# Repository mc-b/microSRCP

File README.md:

microSRCP
=========

microSRCP Projekt, Steuerung einer Modelleisenbahn auf Basis der Arduino Plattform

Dieses Projekt löst das microSRCP Projekt auf berlios.de ab.

Kurzinstallation:
- Arduino Entwicklungsumgebung - http://arduino.cc/en/Main/Software, ab Version 1.0.5 installieren
- RocRail - http://wiki.rocrail.net/doku.php, zur Ansteuerung der Modelleisenbahn und der Arduino's, installieren
- Arduino Entwicklungsumgebung starten und Verzeichnis aus Menu -> Datei -> Einstellungen -> Sketchbook Speicherort notieren
- Entwicklungsumgebung beenden
- gewünschte ZIP/tar-Datei von https://github.com/mc-b/microSRCP/tags auswählen und downloaden
- ZIP/tar Datei entpacken und die Dateien aus Verzeichnis .../microSRCP/arduino in den vorher notierten Sketchbook Speicherort kopieren.
- Arduino Entwicklungsumgebung starten - unter -> Datei -> Sketchbook -> microSRCPServer wählen
- PC und Arduino mittels USB Kabel verbinden, das Betriebssystem richtet eine neue Serielle Schnittstelle ein (bei Problemen siehe www.arduino.cc)
- Unter Tools -> entsprechendes Board und Serielle Schnittstelle einstellen
- Compilieren und Uploaden des Sketches...
- RocRail starten und unter -> RocRail Eigenschaften neue srcp Zentrale mit Sub Bibliothek RS232 und gleicher Serieller Schnittstelle wie bei der Arduino Entwicklungsumgebung einrichten

Welche Arduino Boards und Shields benötigt werden steht in den entsprechenden Sketches. 

Für eine Detailierte Beschreibung, siehe https://github.com/mc-b/microSRCP/wiki.

Copyright
---------
Die Software untersteht der GNU GPL, siehe entsprechende Copyrights in 
den Sourcen. Da bedeutet u.a., sie kann frei verwendet werden, Aenderungen
und Erweiterungen muessen aber wieder frei zugaenglich sein.
Kommerzielle Produkte, ohne Offenlegung des Codes, sind damit ausgeschlossen!

Haftung
-------
Bei den Bauanleitungen bzw. irgendwelcher Software gibt es keine Haftung fuer 
irgendwelche Schaeden oder Funktionsgarantie, bitte immer nur als Anregung auffassen.
Ich hafte nicht fuer Schaeden, die der Anwender oder Dritte durch die Verwendung der 
Software oder Hardware verursachen oder erleiden. In keinem Fall hafte ich fuer 
entgangenen Umsatz oder Gewinn oder sonstige Vermoegensschaeden die bei der Verwendung 
oder durch die Verwendung dieser Programme oder Anleitungen entstehen koennen.
Und wer mit Strom umgeht, soll sich bitte bei hoeheren Spannung und Stroemen der 
Gefahren bewusst sein. Modellbahn gehoert VDE-technisch zur Kategorie Spielzeug, 
dementsprechend streng sind die Vorschriften. Siehe hierzu auch die 
Sicherheitshinweise des Fremo. 

Die Schaltungen und die Software werden als Anregung und Hilfe unter Modellbahnern
veroeffentlicht. Sie sind auf Grund von Beispielen aus dem Netz bzw. eigenen Ideen 
entstanden. Natuerlich sind sinnvolle Anregungen, Fehlermeldungen und 
Verbesserungen zu den Schaltung immer willkommen. Allerdings moechte ich aus 
gegebenen Anlass darauf hinweisen, dass ich leider keine Zeit fuer langwierige 
Diskussionen des Typs "Ich habe die Schaltung nachgebaut, warum funktioniert 
sie bei mir nicht" habe. Auch die Frage "Ich habe noch diesen oder jenen Chip 
in der Schublade, kann ich den auch verwenden", moege sich bitte jeder selbst 
beantworten. Kontaktaufnahme bitte per mail und nicht per Telefon. 
Bitte bei Problemen moeglichst exakt schildern, was wie schief geht, 
am besten mit logfiles bzw. exakter Fehlermeldung.

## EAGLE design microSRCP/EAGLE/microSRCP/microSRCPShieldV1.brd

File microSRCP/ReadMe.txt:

Sourcen fuer Arduino IDE und Beispieldateien RocRail.

Arduino IDE
-----------
Dateien aus dem microSRCP/arduino Verzeichnis in Arduino Sketchbook-
Verzeichnis kopieren (siehe File -> Preferences in der 
Arduino IDE).

Mittels File -> Sketchbook koennen dann die einzelne
Board Sketches geoeffnet, compiliert und ins Board
geladen werden.

RocRail
-------
Die SRCP Zentrale kann einfach mittels dem User-Interface von 
RocRail erstellt werden.

Dazu ist eine srcp Zentrale einzutragen und je nach Sketch
die Sub Bibliothek TCPIP oder RS232 einzutragen.

In den Verzeichnissen RocRail befinden sich Beispiele der
rocrail.ini (Konfiguration Zentrale) und dazupassende
plan.xml Dateien.

Copyright
---------
Die Software untersteht der GNU GPL, siehe entsprechende Copyrights in 
den Sourcen. Da bedeutet u.a., sie kann frei verwendet werden, Aenderungen
und Erweiterungen muessen aber wieder frei zugaenglich sein.
Kommerzielle Produkte, ohne Offenlegung des Codes, sind damit ausgeschlossen!

Haftung
-------
Bei den Bauanleitungen bzw. irgendwelcher Software gibt es keine Haftung fuer 
irgendwelche Schaeden oder Funktionsgarantie, bitte immer nur als Anregung auffassen.
Ich hafte nicht fuer Schaeden, die der Anwender oder Dritte durch die Verwendung der 
Software oder Hardware verursachen oder erleiden. In keinem Fall hafte ich fuer 
entgangenen Umsatz oder Gewinn oder sonstige Vermoegensschaeden die bei der Verwendung 
oder durch die Verwendung dieser Programme oder Anleitungen entstehen koennen.
Und wer mit Strom umgeht, soll sich bitte bei hoeheren Spannung und Stroemen der 
Gefahren bewusst sein. Modellbahn gehoert VDE-technisch zur Kategorie Spielzeug, 
dementsprechend streng sind die Vorschriften. Siehe hierzu auch die 
Sicherheitshinweise des Fremo. 

Die Schaltungen und die Software werden als Anregung und Hilfe unter Modellbahnern
veroeffentlicht. Sie sind auf Grund von Beispielen aus dem Netz bzw. eigenen Ideen 
entstanden. Natuerlich sind sinnvolle Anregungen, Fehlermeldungen und 
Verbesserungen zu den Schaltung immer willkommen. Allerdings moechte ich aus 
gegebenen Anlass darauf hinweisen, dass ich leider keine Zeit fuer langwierige 
Diskussionen des Typs "Ich habe die Schaltung nachgebaut, warum funktioniert 
sie bei mir nicht" habe. Auch die Frage "Ich habe noch diesen oder jenen Chip 
in der Schublade, kann ich den auch verwenden", moege sich bitte jeder selbst 
beantworten. Kontaktaufnahme bitte per mail und nicht per Telefon. 
Bitte bei Problemen moeglichst exakt schildern, was wie schief geht, 
am besten mit logfiles bzw. exakter Fehlermeldung. 

8. Mai 2013 / Marcel Bernet

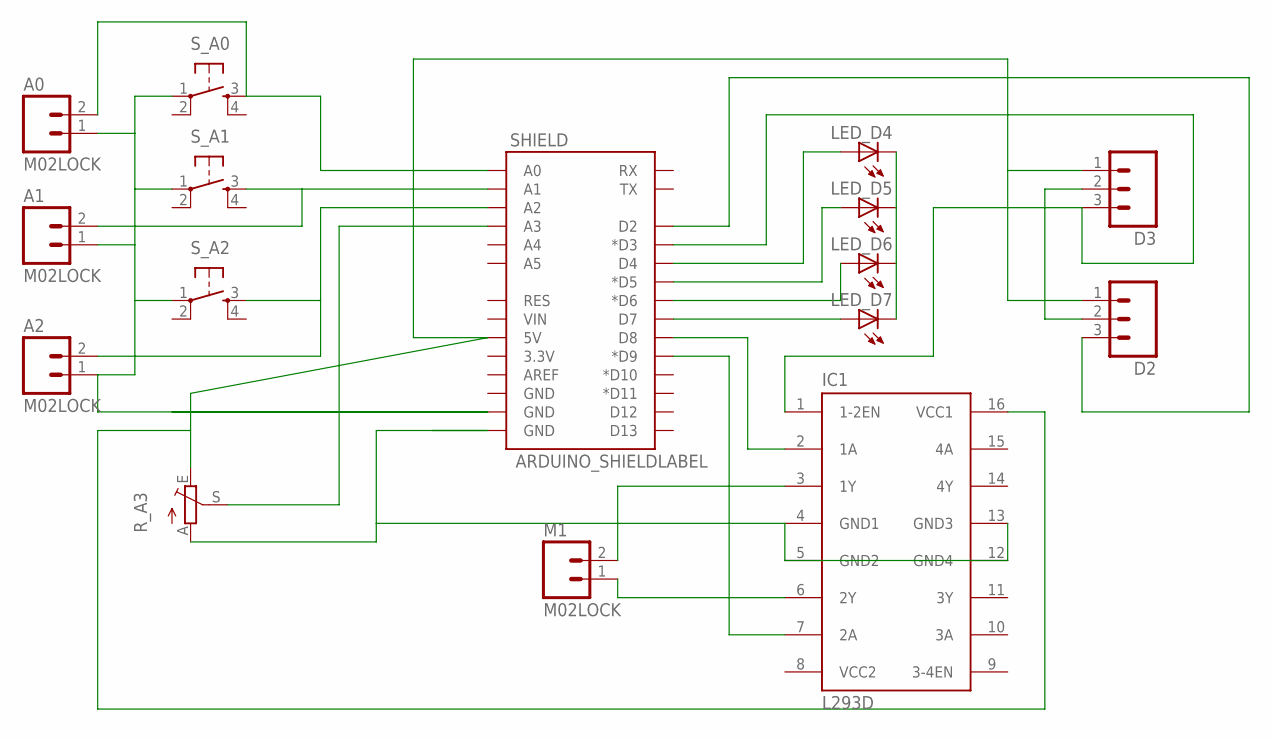
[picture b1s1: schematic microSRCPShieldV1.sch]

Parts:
A0, A1, A2: M02LOCK; 1X02_LOCK
D2, D3: M03LOCK; 1X03_LOCK
IC1: L293D; DIL16
LED_D4, LED_D5, LED_D6, LED_D7: LED3MM
M1: M02LOCK; 1X02_LOCK
R_A3: TRIM_EU-PT10S; PT-10S
SHIELD: ARDUINO_SHIELDLABEL; DUEMILANOVE_SHIELD
S_A0, S_A1, S_A2: TAC_SWITCHPTH; TACTILE-PTH

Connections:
unnamed: A1.2, SHIELD.A1, S_A1.3
unnamed: LED_D6.A, SHIELD.D6 (*D6)
unnamed: LED_D5.A, SHIELD.D5 (*D5)
unnamed: LED_D4.A, SHIELD.D4
unnamed: LED_D4.K (C), LED_D5.K (C), LED_D6.K (C), LED_D7.K (C)
unnamed: A2.2, SHIELD.A2, S_A2.3
unnamed: LED_D7.A, SHIELD.D7
unnamed: A0.2, SHIELD.A0, S_A0.3
unnamed: IC1.2 (1A), SHIELD.D8
unnamed: IC1.7 (2A), SHIELD.D9 (*D9)
unnamed: D2.1, D3.1, IC1.16 (VCC1), R_A3.E, SHIELD.5V
unnamed: IC1.3 (1Y), M1.2
unnamed: IC1.6 (2Y), M1.1
unnamed: R_A3.S, SHIELD.A3
unnamed: A0.1, A1.1, A2.1, SHIELD.GND@1 (GND), S_A0.1, S_A1.1, S_A2.1
unnamed: IC1.4 (GND1), IC1.5 (GND2), IC1.12 (GND4), IC1.13 (GND3), R_A3.A, SHIELD.GND@0 (GND)
unnamed: D2.3, SHIELD.D2
unnamed: D3.3, IC1.1 (1-2EN), SHIELD.D3 (*D3)
unnamed: D2.2, D3.2
VCC2: IC1.8 (VCC2)

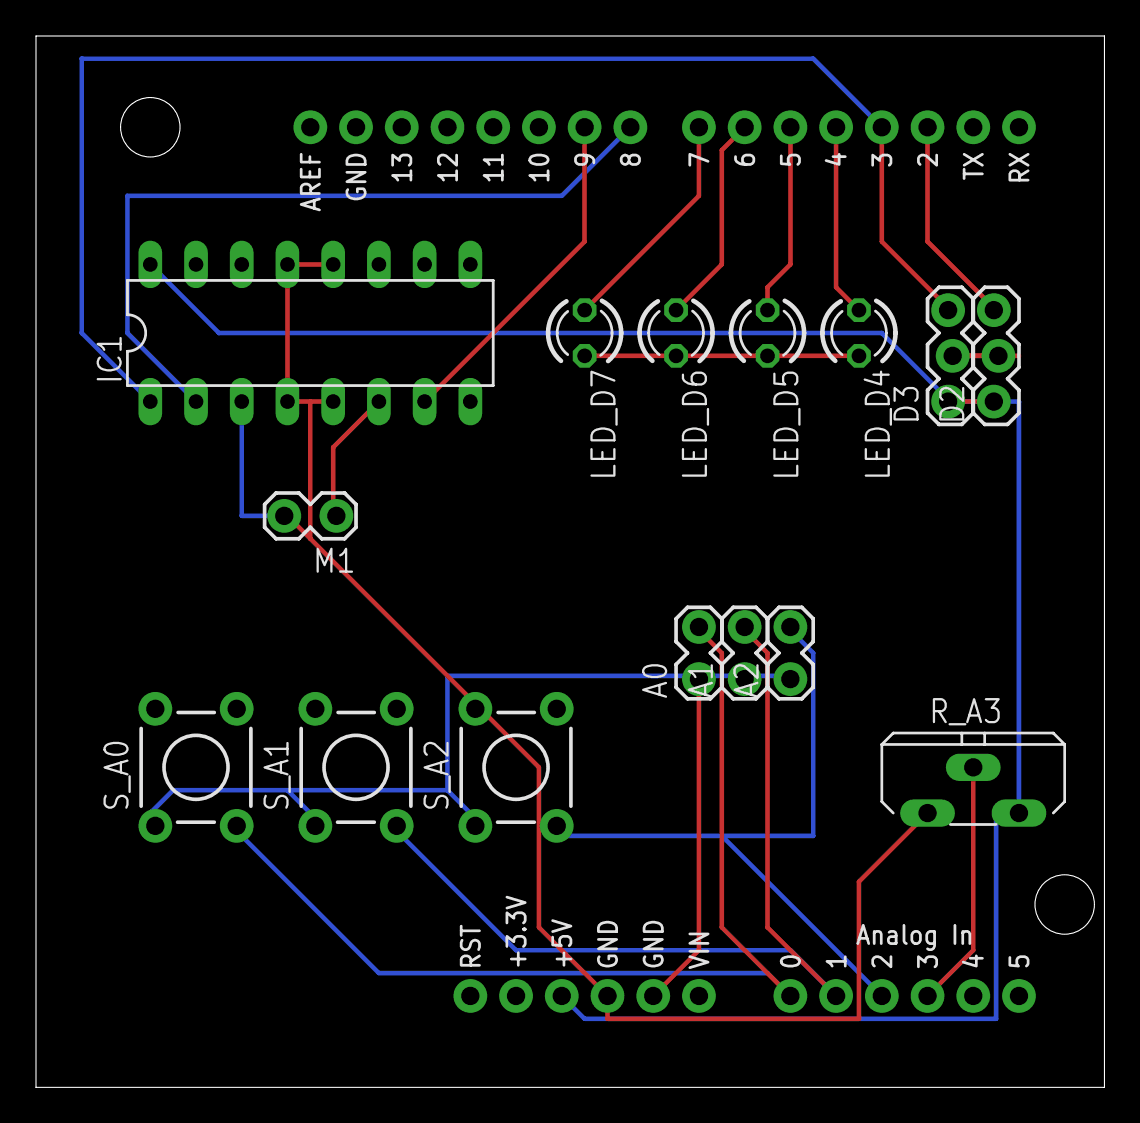
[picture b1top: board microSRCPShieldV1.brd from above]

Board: 2 copper layers, 59.4 x 58.4 mm, 16 parts (0 on the bottom side), 19 nets.

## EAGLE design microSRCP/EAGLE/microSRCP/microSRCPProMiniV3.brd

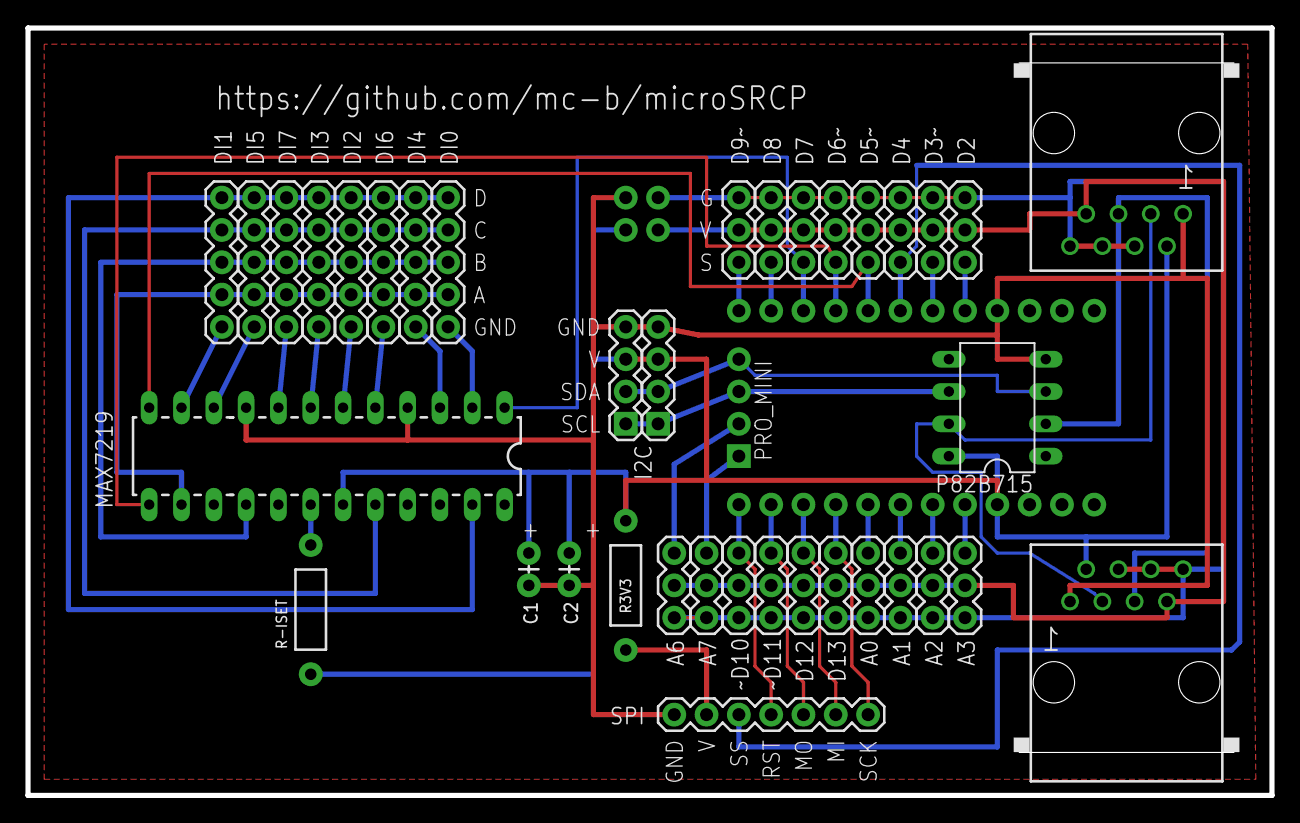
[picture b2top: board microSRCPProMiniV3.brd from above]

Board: 2 copper layers, 97.8 x 60.3 mm, 41 parts (0 on the bottom side), 40 nets.

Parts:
A0, A1, A2, A3, A6, A7: 1X03
C1, C2: AXIAL-0.1
D2, D3~, D4, D5~, D6~, D7, D8, D9~, D12, D13: 1X03
DI0, DI1, DI2, DI3, DI4, DI5, DI6, DI7: 1X05
E$1: 1X04_NO_SILK
E$2: 1X04
E$3: R3V3; AXIAL-0.4
E$4, E$5: RJ45-NO-SHIELD
GND: 1X02_NO_SILK
I2C: 1X04
MAX7219: DIL24
P82B715: DIL-08
PRO_MINI: ARDUINO_MINI
R-ISET: AXIAL-0.4
SPI: 1X07
V5: 1X02_NO_SILK
~D10, ~D11: 1X03

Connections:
2-5V: A0.2, A1.2, A2.2, A3.2, A6.2, A7.2, D2.2, D3~.2, D4.2, D5~.2, D6~.2, D7.2, D8.2, D9~.2, D12.2, D13.2, E$4.7, E$5.7, GND.1, ~D10.2, ~D11.2
2-GND: A0.1, A1.1, A2.1, A3.1, A6.1, A7.1, D2.3, D3~.3, D4.3, D5~.3, D6~.3, D7.3, D8.3, D9~.3, D12.1, D13.1, E$4.4, E$4.6, E$4.8, E$5.4, E$5.6, E$5.8, GND.2, ~D10.1, ~D11.1
5V: C1.P$2, C2.P$2, E$2.3, E$3.P$2, E$4.2, E$5.2, I2C.3, MAX7219.19, P82B715.8, PRO_MINI.21, R-ISET.P$1, V5.1
GND: C1.P$1, C2.P$1, E$2.4, E$4.1, E$5.1, I2C.4, MAX7219.4, MAX7219.9, P82B715.4, PRO_MINI.4, SPI.1, V5.2
LSDA: E$4.5, E$5.5, P82B715.2
LSDL: E$4.3, E$5.3, P82B715.7
S$1: E$3.P$1, SPI.2
S$2: D2.1, PRO_MINI.5
S$3: D3~.1, PRO_MINI.6
S$4: D4.1, PRO_MINI.7, SPI.3
S$5: D5~.1, MAX7219.12, PRO_MINI.8
S$6: D6~.1, MAX7219.13, PRO_MINI.9
S$7: D7.1, MAX7219.1, PRO_MINI.10
S$8: D8.1, PRO_MINI.11
S$9: D9~.1, PRO_MINI.12
S$10: PRO_MINI.13, SPI.4, ~D10.3
S$11: PRO_MINI.14, SPI.5, ~D11.3
S$12: D12.3, PRO_MINI.15, SPI.6
S$13: D13.3, PRO_MINI.16, SPI.7
S$14: A0.3, PRO_MINI.17
S$15: A1.3, PRO_MINI.18
S$16: A2.3, PRO_MINI.19
S$17: A3.3, PRO_MINI.20
S$18: DI0.1, MAX7219.2
S$19: DI4.1, MAX7219.3
S$20: DI6.1, MAX7219.5
S$21: DI2.1, MAX7219.6
S$22: DI3.1, MAX7219.7
S$23: DI7.1, MAX7219.8
S$24: DI5.1, MAX7219.10
S$25: DI1.1, MAX7219.11
S$26: DI0.2, DI1.2, DI2.2, DI3.2, DI4.2, DI5.2, DI6.2, DI7.2, MAX7219.14
S$27: MAX7219.18, R-ISET.P$2
S$28: DI0.4, DI1.4, DI2.4, DI3.4, DI4.4, DI5.4, DI6.4, DI7.4, MAX7219.20
S$29: DI0.5, DI1.5, DI2.5, DI3.5, DI4.5, DI5.5, DI6.5, DI7.5, MAX7219.23
S$32: DI0.3, DI1.3, DI2.3, DI3.3, DI4.3, DI5.3, DI6.3, DI7.3, MAX7219.16
S$A6: A6.3, E$1.2
S$A7: A7.3, E$1.1
SDA: E$1.4, E$2.2, I2C.2, P82B715.3
SDL: E$1.3, E$2.1, I2C.1, P82B715.6

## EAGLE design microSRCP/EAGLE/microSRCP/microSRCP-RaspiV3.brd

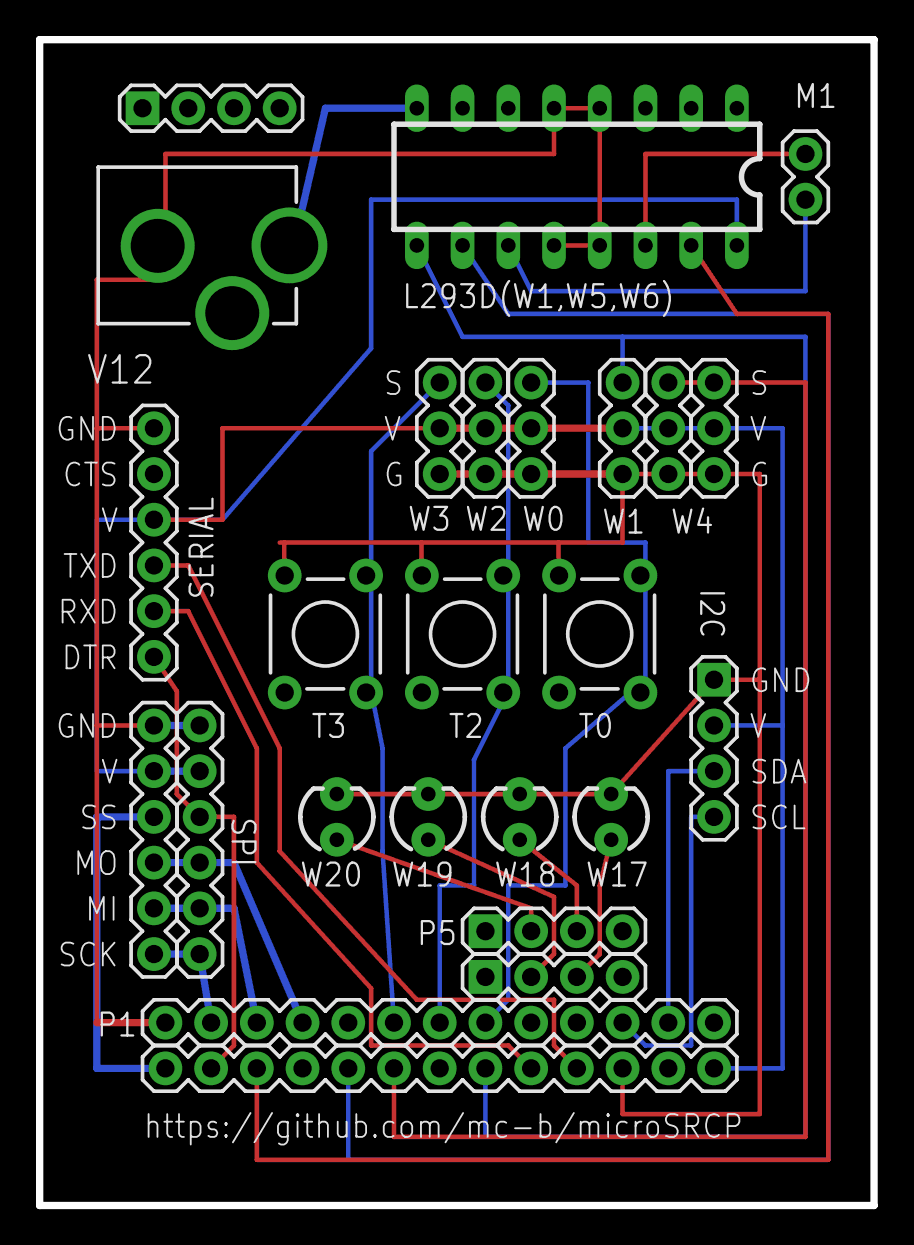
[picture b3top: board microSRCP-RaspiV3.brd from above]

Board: 2 copper layers, 46.4 x 64.8 mm, 25 parts (0 on the bottom side), 24 nets.

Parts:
E$1: 1X13
E$2, E$3: 1X04
E$5: 1X06
I2C: 1X04
L293D(W1,W5,W6): DIL16
M1: 1X02
P1: 1X13
P5: 1X04
SERIAL: 1X06
SPI: 1X06
T0, T2, T3: TACTILE-PTH
V12: POWER_JACK_PTH_LOCK
W0, W1, W1N, W2, W3, W4: 1X03
W17, W18, W19, W20: LED3MM

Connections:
5V: E$1.13, E$5.5, I2C.2, L293D(W1,W5,W6).16, SERIAL.4, SPI.2, W0.2, W1.2, W1N.2, W2.2, W3.2, W4.2
GND: E$1.11, E$5.6, I2C.1, L293D(W1,W5,W6).4, L293D(W1,W5,W6).5, L293D(W1,W5,W6).12, L293D(W1,W5,W6).13, P1.1, SERIAL.6, SPI.1, W0.1, W1.1, W1N.1, W2.1, W3.1, W4.1, W17.K, W18.K, W19.K, W20.K
S0: P1.8, W0.3
S1: E$1.8, L293D(W1,W5,W6).9, W4.3
S2: P1.7, W2.3
S3: P1.6, W3.3
S4: E$1.6, W1.3, W1N.3
S5: E$1.5, L293D(W1,W5,W6).10
S6: E$1.3, L293D(W1,W5,W6).15
S$2: E$5.1, P1.2, SPI.6
S$3: E$5.2, P1.3, SPI.5
S$4: E$5.3, P1.4, SPI.4
S$5: E$1.1, SPI.3
S$6: E$1.2, E$5.4, SERIAL.1
S$8: E$3.3, W17.A
S$10: P5.3, W18.A
S$11: E$3.2, W19.A
S$12: P5.2, W20.A
S$13: E$1.9, SERIAL.2
S$14: E$1.10, SERIAL.3
SM1L: L293D(W1,W5,W6).14, M1.1
SM1R: L293D(W1,W5,W6).11, M1.2
SSCL: I2C.4, P1.11
SSDA: I2C.3, P1.12

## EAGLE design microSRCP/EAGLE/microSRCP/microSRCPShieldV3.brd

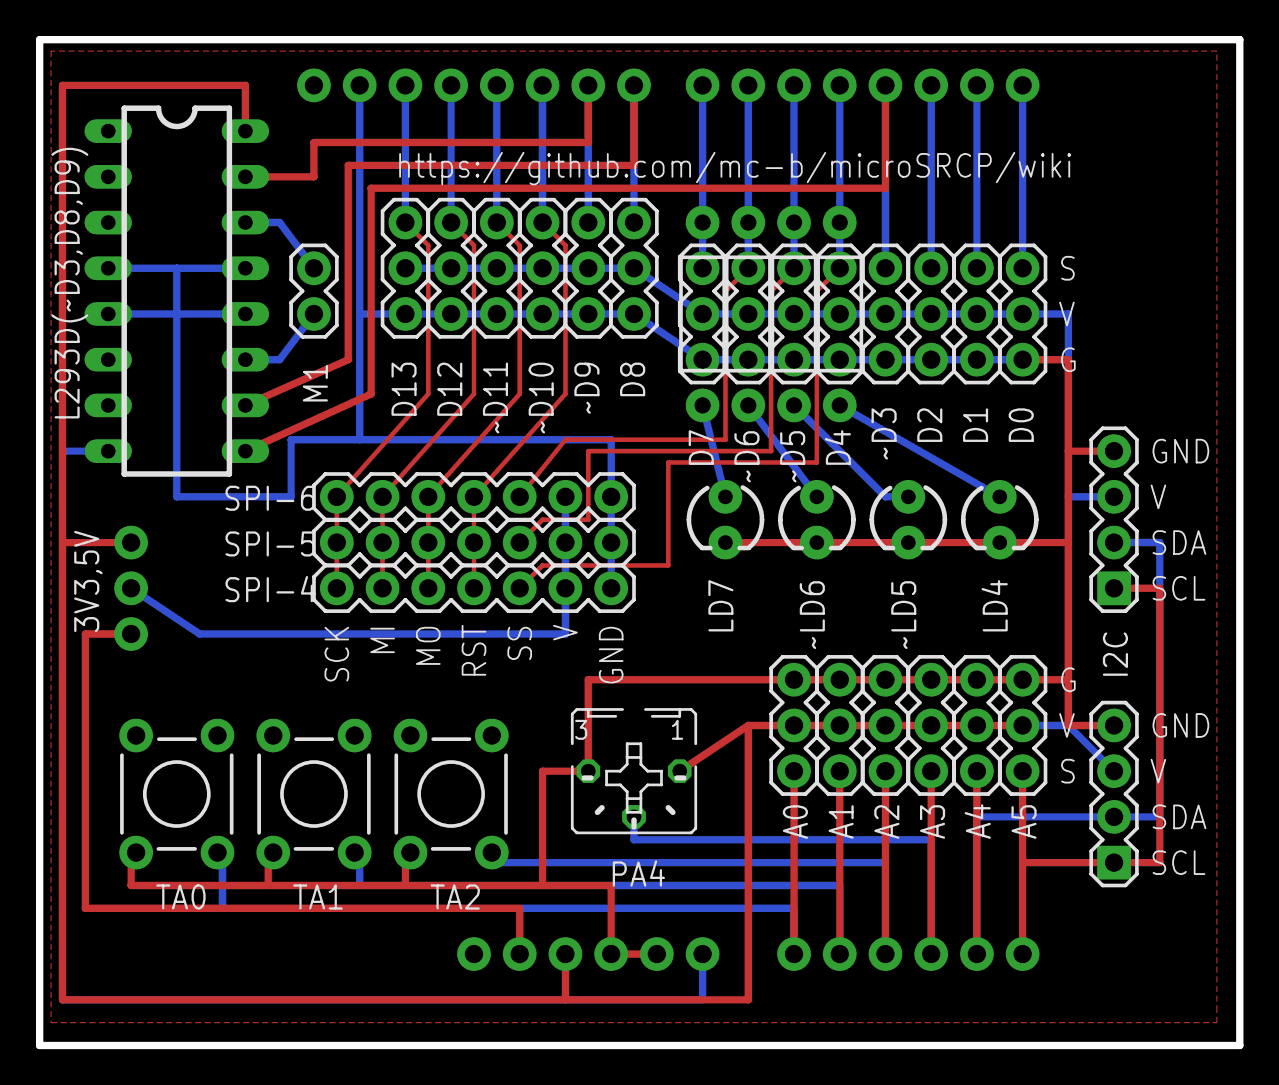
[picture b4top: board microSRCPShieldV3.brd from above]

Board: 2 copper layers, 66.7 x 55.9 mm, 41 parts (0 on the bottom side), 31 nets.

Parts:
3V3,5V: 1X03_NO_SILK
A0, A1, A2, A3, A4, A5: 1X03
D0, D1, D2, D4, D7, D8, D12, D13: 1X03
E$1: DUEMILANOVE_SHIELD_NOHOLES_NOLABELS
I2C, I2C-2: 1X04
L293D(~D3,D8,D9): DIL16
LD4, LD7: LED3MM
M1: 1X02
PA4: B25P
R1, R2, R3, R7: AXIAL-0.4
SPI-4, SPI-5, SPI-6: 1X07
TA0, TA1, TA2: TACTILE-PTH
~D3, ~D5, ~D6, ~D9, ~D10, ~D11: 1X03
~LD5, ~LD6: LED3MM

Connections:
GND: A0.3, A1.3, A2.3, A3.3, A4.3, A5.3, D0.3, D1.3, D2.3, D4.3, D7.3, D8.3, D12.3, D13.3, E$1.GND@0, E$1.GND@1, E$1.GND@2, I2C.4, I2C-2.4, L293D(~D3,D8,D9).4, L293D(~D3,D8,D9).5, L293D(~D3,D8,D9).12, L293D(~D3,D8,D9).13, LD4.K, LD7.K, PA4.E, SPI-4.7, SPI-5.7, SPI-6.7, ~D3.3, ~D5.3, ~D6.3, ~D9.3, ~D10.3, ~D11.3, ~LD5.K, ~LD6.K
S0: D0.1, E$1.RX
S1: D1.1, E$1.TX
S2: D2.1, E$1.D2
S3: E$1.D3, L293D(~D3,D8,D9).9, ~D3.1
S3V3: 3V3,5V.1, E$1.3.3V
S5: E$1.D5, R2.P$2, SPI-5.5, ~D5.1
S6: E$1.D6, R1.P$2, SPI-6.5, ~D6.1
S7: D7.1, E$1.D7, R7.P$2
S8: D8.1, E$1.D8, L293D(~D3,D8,D9).10
S10: E$1.D10, SPI-4.4, SPI-5.4, SPI-6.4, ~D10.1
S11: E$1.D11, SPI-4.3, SPI-5.3, SPI-6.3, ~D11.1
S12: D12.1, E$1.D12, SPI-4.2, SPI-5.2, SPI-6.2
S13: D13.1, E$1.D13, SPI-4.1, SPI-5.1, SPI-6.1
S$1: R2.P$1, ~LD5.A
S$2: 3V3,5V.2, SPI-4.6, SPI-5.6, SPI-6.6
S$3: E$1.D9, L293D(~D3,D8,D9).15, ~D9.1
S$4: D4.1, E$1.D4, R3.P$2, SPI-4.5
S$9: LD4.A, R3.P$1
S$11: R1.P$1, ~LD6.A
S$12: LD7.A, R7.P$1
SA0: A0.1, E$1.A0
SA1: A1.1, E$1.A1
SA2: A2.1, E$1.A2
SA3: A3.1, E$1.A3, PA4.S
SA4: A4.1, E$1.A4, I2C.2, I2C-2.2
SA5: A5.1, E$1.A5, I2C.1, I2C-2.1
SM1-L: L293D(~D3,D8,D9).14, M1.2
SM1R: L293D(~D3,D8,D9).11, M1.1
SVIN: E$1.VIN, L293D(~D3,D8,D9).8
V5O: 3V3,5V.3, A0.2, A1.2, A2.2, A3.2, A4.2, A5.2, D0.2, D1.2, D2.2, D4.2, D7.2, D8.2, D12.2, D13.2, E$1.5V, I2C.3, I2C-2.3, L293D(~D3,D8,D9).16, PA4.A, ~D3.2, ~D5.2, ~D6.2, ~D9.2, ~D10.2, ~D11.2

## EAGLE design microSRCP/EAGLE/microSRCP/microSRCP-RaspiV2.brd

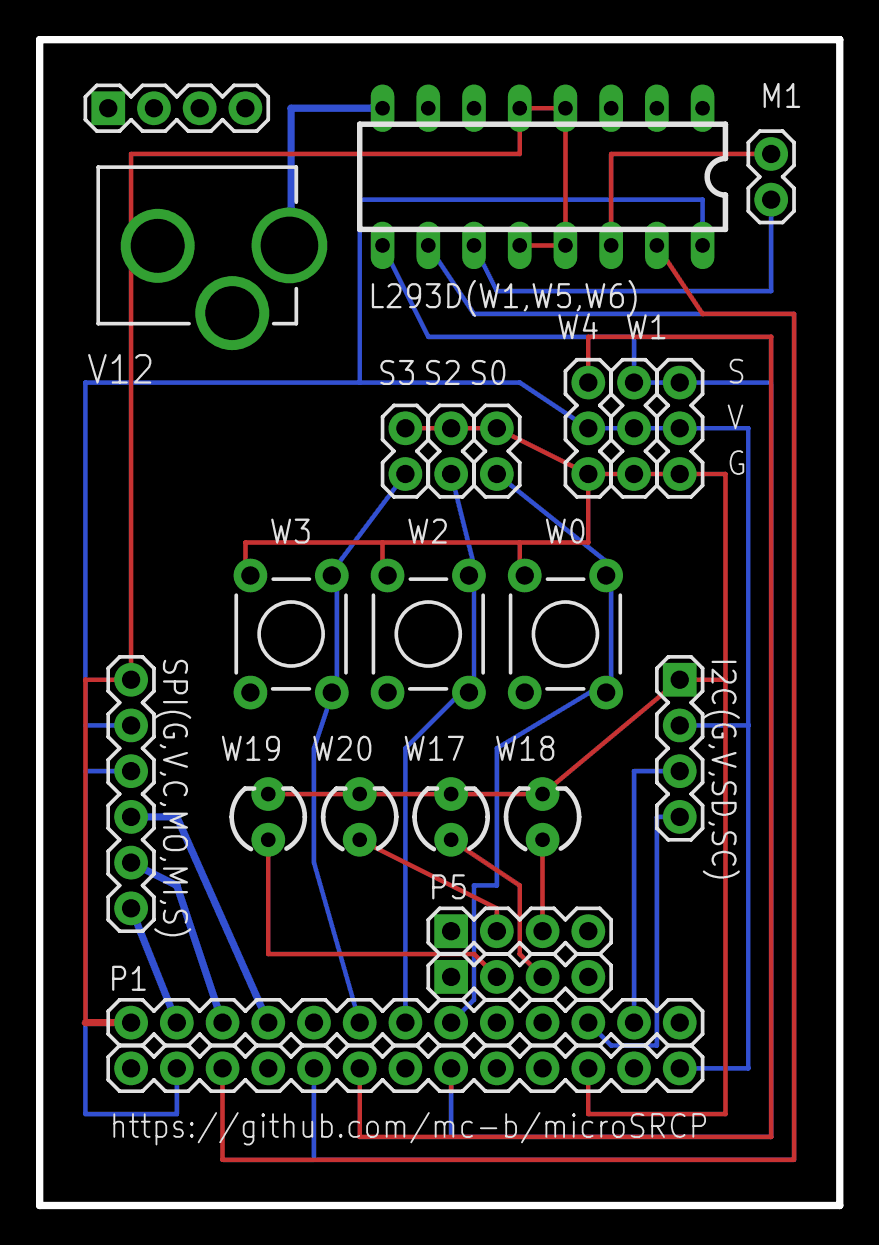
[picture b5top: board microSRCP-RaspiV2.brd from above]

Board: 2 copper layers, 44.4 x 64.8 mm, 23 parts (0 on the bottom side), 22 nets.

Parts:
E$1: 1X13
E$2, E$3: 1X04
I2C(G,V,SD,SC): 1X04
L293D(W1,W5,W6): DIL16
M1: 1X02
P1: 1X13
P5: 1X04
S0, S2, S3: 1X02
SPI(G,V,C,MO,MI,S): 1X06
V12: POWER_JACK_PTH_LOCK
W0, W2, W3: TACTILE-PTH
W1, W1N, W4: 1X03
W17, W18, W19, W20: LED3MM

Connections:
5V: E$1.13, I2C(G,V,SD,SC).2, L293D(W1,W5,W6).16, SPI(G,V,C,MO,MI,S).2, W1.2, W1N.2, W4.2
GND: E$1.11, I2C(G,V,SD,SC).1, S0.2, S2.2, S3.2, W1.1, W1N.1, W4.1, W17.K, W18.K, W19.K, W20.K
GND2: L293D(W1,W5,W6).4, L293D(W1,W5,W6).5, L293D(W1,W5,W6).12, L293D(W1,W5,W6).13, P1.1, SPI(G,V,C,MO,MI,S).1
S0: P1.8, S0.1
S1: E$1.8, L293D(W1,W5,W6).9, W1.3, W1N.3
S2: P1.7, S2.1
S3: P1.6, S3.1
S4: E$1.6, W4.3
S5: E$1.5, L293D(W1,W5,W6).10
S6: E$1.3, L293D(W1,W5,W6).15
S17: P5.3, W18.A
S18: E$3.3, W17.A
S19: P5.2, W20.A
S20: E$3.2, W19.A
SCE0: E$1.2, SPI(G,V,C,MO,MI,S).3
SM1L: L293D(W1,W5,W6).14, M1.1
SM1R: L293D(W1,W5,W6).11, M1.2
SMISO: P1.3, SPI(G,V,C,MO,MI,S).5
SMOSI: P1.4, SPI(G,V,C,MO,MI,S).4
SSCL: I2C(G,V,SD,SC).4, P1.11
SSCLK: P1.2, SPI(G,V,C,MO,MI,S).6
SSDA: I2C(G,V,SD,SC).3, P1.12

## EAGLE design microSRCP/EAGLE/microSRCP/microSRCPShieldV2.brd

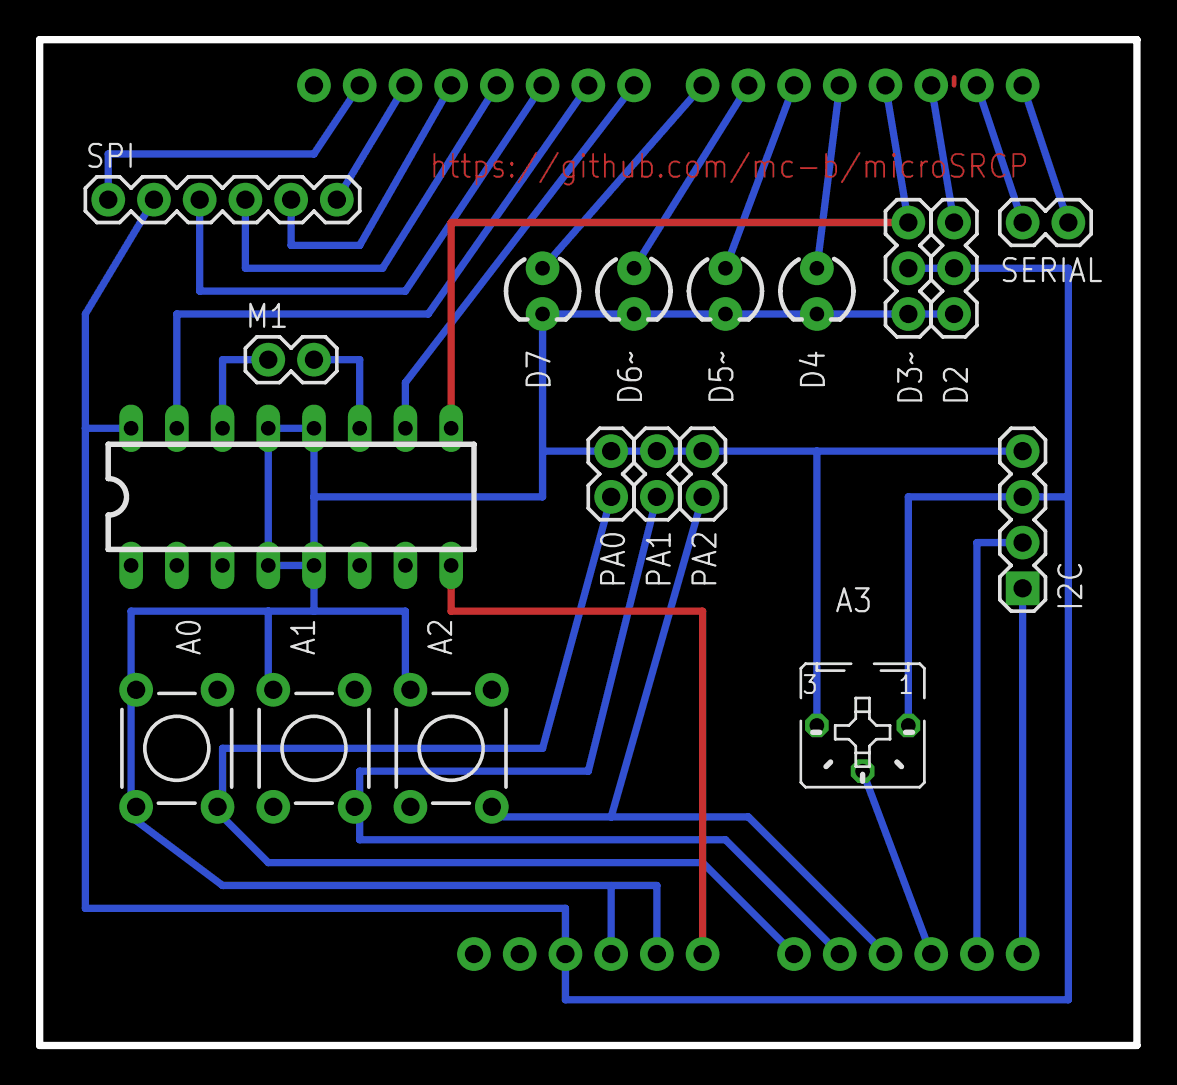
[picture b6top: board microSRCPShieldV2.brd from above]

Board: 2 copper layers, 61.0 x 55.9 mm, 19 parts (0 on the bottom side), 25 nets.

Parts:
1: L293D; DIL16
90: DUEMILANOVE_SHIELD_NOHOLES_NOLABELS
A0, A1, A2: TACTILE-PTH
A3: B25P
D2, D3~: 1X03
D4, D5~, D6~, D7: LED3MM
I2C: 1X04
M1: 1X02
PA0, PA1, PA2: 1X02
SERIAL: 1X02
SPI: 1X06

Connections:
5V: 1.16, 90.5V, A3.A, D2.2, D3~.2, I2C.3, SPI.2
GND: 1.4, 1.5, 1.12, 1.13, 90.GND@0, 90.GND@1, A3.E, D2.1, D3~.1, D4.K, D5~.K, D6~.K, D7.K, I2C.4, PA0.2, PA1.2, PA2.2
GND2: 90.GND@2, SPI.1
S$1: 90.D10, SPI.3
S$2: 90.A5, I2C.1
S$3: 1.15, 90.D9
S$4: 90.D13, SPI.6
S$5: 90.D7, D7.A
S$6: 90.D6, D6~.A
S$7: 90.D5, D5~.A
S$8: 90.D4, D4.A
S$9: 1.9, 90.D3, D3~.3
S$10: 90.D2, D2.3
S$11: 90.D12, SPI.5
S$12: 90.TX, SERIAL.1
S$13: 90.RX, SERIAL.2
S$14: 90.D11, SPI.4
S$16: 90.A4, I2C.2
S$17: 90.A0, PA0.1
S$19: 90.A2, PA2.1
S$21: 90.A3, A3.S
S$22: 1.11, M1.2
S$24: 1.14, M1.1
S$25: 1.10, 90.D8
VIN: 1.8, 90.VIN

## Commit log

2013-05-26 Update ReadMe.txt
    RocRail Zentrale geaendert
2013-05-27 Ethernet Libraries
2013-05-27 Werden im Standard nicht benoetigt
2013-05-27 Grundschaltung inkl. Test
2013-05-27 Serielle SRCP I/O Abhandlung, ohne FB
2013-05-28 GASignal durch GALed ersetzt Erste Protokollversuche
2013-05-28 Integration Ethernet SRCP Server
2013-05-28 Feintuning damit es auch in der Arduino IDE laeuft
2013-05-28 Arduino IDE Umgebung, gleiche Sourcen bis auf microSRCPGL welche nach pde umbenannt und Anpassen der Includes
2013-05-28 Angepasst an Arduino IDE inkl. Ausgabe von Debugging Informationen
2013-05-28 Installationsanweisungen angepasst
2013-05-28 Update README.md
    Schnelleinstieg
2013-05-28 Konfigurationen gesaeubert, Logdateien zur Auswertung hinzugefuegt.
2013-05-29 flush I/O Seriell
2013-05-29 Feintuning Serieller I/O
2013-05-29 Serieller I/O aktiviert, Servo Adressen korrigiert
2013-05-29 Servo Adressen korrigiert
2013-05-29 Log zum RocRail Trace
2013-05-29 Anpassungen fuer RocRail 5327
2013-05-29 Detailkorrekturen - Servo schaltete nicht, Led falsch herum angesteuert
2013-05-31 Aktualisierte Images
2013-06-01 I2C Grundgeruest
2013-06-01 Unschoenheit mit globalem cmd Buffer eleminiert
2013-06-01 Backup Dateien nicht einchecken
2013-06-01 Globale cmd Buffer eleminiert
2013-06-01 Protokoll wird jetzt mittels #define eingestellt, erspart mehrere Sketches.
2013-06-01 getDescription fuer I2C Bus implementiert
2013-06-01 I2C Grundgeruest - nicht getestet
2013-06-02 I2C Umbau - 1. Teil
2013-06-02 Code nachgefuehrt
2013-06-02 Korrekturen und Tests fuer I2C Schnittstelle
2013-06-03 Totalumbau I2C Adressierung der lokalen Geraete
2013-06-03 I2C Bus Feinschliff und Tests der Geraete
2013-06-03 Handshacking korrigiert, fehlte \n
2013-06-03 Sensoren werden nur noch alle 500 Millis abgefragt, weniger Trafik auf dem I2C Bus
2013-06-03 Feinschliff
2013-06-03 Revert "Feinschliff"
    This reverts commit b7f99655d7eff1f953f46f5b50a3e4c23fd93f71.
2013-06-03 DCC Board - Alpha Variante
2013-06-03 Beispiel fuer ein I2C Slave Board
2013-06-03 Sketch inkl. Libraries fuer DCC Board
2013-06-03 Anpassungen an Arduino IDE
2013-06-05 Trace RocRail - Arduino
2013-06-05 Neue Loks fuer DCC Tests
2013-06-05 Kombination OpenDCC Code und microSRCP
2013-06-05 Minimales Beispiel fuer das lesen und behandeln von SRCP Befehlen
2013-06-05 Einfaches SRCP Beispiel erweitert um Led's und Servo
2013-06-06 I2C Beispiel
2013-06-06 Beispiel I2C Verkabelung
2013-06-06 Beispiel OpenDCC Booster Shield
2013-06-06 GASignal funktioniert jetzt mittels Adresse und Port = Led
2013-06-06 refresh() ueber alle Geraete auch GA und GL Beispiel fuer eine blinkende Led unter Verwendung von refresh()
2013-06-07 Implementierung Wave Shield
2013-06-07 Unnoetiger Code entfernt
2013-06-07 Geraet fuer langsamen Servowechsel
2013-06-08 Anfangsruckeln eleminiert An- und Abschalten des Servos wenn nicht gebraucht
2013-06-08 Es gibt nur noch die Core Sourcen unter microSRCP/arduino/libraries - microSRCPCore/src linkt dorthin
2013-06-08 Implementierung Wechselblinklicht
2013-06-08 delay() aus loop() Methode entfernt, stoert Multitasking
2013-06-09 Sprechendere Namen verwendet
2013-06-09 Dokumentation nachgefuehrt
2013-06-09 Debugging per default - deaktiviert
2013-06-10 Optimierungen fuer Raspberry PI
2013-06-10 SRCPEthernetServer umbenannt und verschoben nach lan - um Probleme mit Arduino IDE 1.0.1 zu vermeiden
2013-06-10 Anpassungen damit es auf Linux auch compiliert
2013-06-12 Bessere Bezeichnungen - Proxy statt Master
2013-06-12 Klarstellungen bei Namen um Konflikte zwischen ODCC und DCC zu vermeiden
2013-06-12 Sourcen sind nur noch in arduino/libraries
2013-06-12 Anzeige freeRAM in INFO POWER Meldung
2013-06-12 freeRAM aus Namespace srcp entfernt
2013-06-12 I2C Bus - delay vermindert wie alte Version 10 millis lesen und 5 millis schreiben
2013-06-12 Weniger Debugging-Infos
2013-06-12 Unnoetige Debugging Infos raus
2013-06-12 Beispiel Motorentreiber
2013-06-12 Umbau Motor Shield - Variante 1
2013-06-13 Bilder aktualisiert
2013-06-13 Fehlerhafte Bilder korrigiert
2013-06-13 Bilder korrigiert
2013-06-13 MotorenShields Geraete bereinigt
2013-06-14 Neuer Board Layout - basierend auf einer Eigenentwicklung
2013-06-14 Update README.md
    Kurzinstallation verbessert
2013-06-14 Variable Angaben von Anzahl I2C Slaves und Sensor Polling eingebaut
2013-06-14 Falscher Default Wert fuer die Kommunikation
2013-06-15 Zentrale als Layout
2013-06-15 Debugging Ausgaben braucht nicht mehr Streaming.h
2013-06-15 Alte Logdateien entfernt
2013-06-15 Beispiel fuer weitere Board Layouts
2013-06-16 Falsche FB Startadresse, korrigiert
2013-06-16 Neues GL Board
2013-06-16 Beide DCC Varianten funktionieren jetzt auch als I2C Slave
2013-06-19 Totalumbau von Debugging Meldungen
2013-06-19 Kommentare in den Header ausgebaut, unnoetige Projekte geloescht um Doppelspurigkeiten mit Sketches auf ein minimum zu Beschraenken
2013-06-19 Debugging Ausgaben verschoenert
2013-06-20 Ausgabe der Geraete vereinheitlicht und als Makro implementiert
2013-06-20 Debugging Meldungen: Verstaendlichkeit erhoeht
2013-06-20 Meldungen fuer den I2C Bus optimiert
2013-06-20 Deaktivieren alle Geraete bei Ethernet Variante
2013-06-20 Kleine Schnittstellen Korrekturen
2013-06-20 DEBUG_LEVEL ist Standard Level fuer Mega
2013-06-20 Langsame Servo Ansteuerung ist jetzt Standard
2013-06-20 Download ab getagter Version statt ab Entwicklungsstand
2013-06-21 RaspBerry Pi Einstellungen und Installationsanweisungen
2013-06-22 Jeweils Erklaerungsbild hinzugefuegt
2013-08-17 Es wird das Analog Hilfsregister statt das I2C Register als Zwischenspeicher fuer OpenDCC verwendet
2013-08-22 Bild fuer Input
2013-08-22 Konfigurationsdateien fuer RaspberryPi als WLAN Access Point
2013-08-25 Doku fuer Kurs an Workshoptagen 2013
2013-08-26 Zweitletztes Kapitel mehr ausgearbeitet
2013-08-26 Mehr Details zu RocRail, Firmata und fhem
2013-08-27 Hinweis Fehlerbehebung bei Verwendung mit alter VMWare Umgebung
2013-08-28 Nur Mega mit 2560 haben Debugging eingeschaltet
2013-08-30 Haftung und abgestimmte Verwendungsmoeglichkeiten
2013-08-30 PDF/A Format damit es auf OS/X auch sauber angezeigt wird
2013-09-08 Detailkorrekturen und neue Folien - Elektronik 1 x 1 - DCC
2013-09-09 Folie mit Hausautomation und 220 Volt
2013-09-09 Notizen erweitert, kleine Korrekturen
2013-09-16 Beispiel fuer zwei verbundene Teststrecken
2013-10-03 Falsche Pin Bezeichnungen im Kommentar bereinigt (C0-C3 = A0-A3)
2013-10-07 Raspberry Pi Vorlagen und Konfigurationsdateien
2014-03-28 Unterlagen OSS an Schulen Workshop
2014-03-28 Experimentierboard - CNC Code fuer LinuxCNC CAM
2014-03-28 Kurzvorstellung microSRCP und microHOME - OSS an Schulen
2014-04-05 Erweiterungen fuer Leonardo
2014-04-25 Kurzvortrag ictScope wie Messen wir das Internet der Dinge
2014-04-25 Beispiele zu Kurzvortrag wie misst man das Internet der Dinge
2014-05-30 microSRCP Shield
2014-06-14 Schaltplaene und Layout von eigenen Shields
2014-06-14 Sketches fuer eigene Shields
2014-07-28 microSRCPV2 Board und Sketches
2014-07-28 Sketches aufgeraeumt
2014-07-28 Korrektur Beschriftungen - LED's
2014-07-28 Konfigurationsdatei wird nicht benoetigt
2014-07-28 EAGLE Konfiguration
2014-08-16 microSRCP Shield mit Steckern an allen Pins
2014-08-16 Poti/Speed bei jedem Halt ueberpruefen
2014-08-16 Feinkorrekturen
2014-08-16 Gerber Files raus
2014-08-16 V3 mit gleicher Pin-Belegung wie V2 plus SPI Anschluessen
2014-08-17 Massenflaechen angefuegt
2014-08-17 Shield fuer Arduino Pro Mini - von www.betemcu.cn
2014-08-18 Detailkorrekturen
2014-08-31 Ansteuerung MAX7219 LED Driver
2014-10-01 I2C Register statt Analog Hilfsregister verwenden.
    Durch die Aenderung vom 17. August 2013 funktionierten einige Decoder
    nicht mehr.
2014-11-12 L298N motor driver board module
2014-11-12 Power ON und OFF waren vertauscht
2014-11-12 Leonardo mit OpenDCC - nicht getestet, weil keine Verbindung zu Rocrail
2014-11-15 Unterstuetzung fuer Arduino MEGA
2015-08-01 Problematik mit zwei oder mehr Zentralen geloest
    Werden zwei Zentralen an der Seriellen Schnittstelle angeschlossen, wird
    bei unterschiedlichen Arduino's die schneller Zentrale nicht sauber
    initialisert. Das aeussert sich dadurch, dass bei der ersten Zentrale
    keine Rueckmelder gemeldet werden.
2016-03-28 Aktualisiert

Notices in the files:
parts and their libraries:
SparkFun-Connectors: Licensing: Creative Commons ShareAlike 4.0 International - https://creativecommons.org/licenses/by-sa/4.0
